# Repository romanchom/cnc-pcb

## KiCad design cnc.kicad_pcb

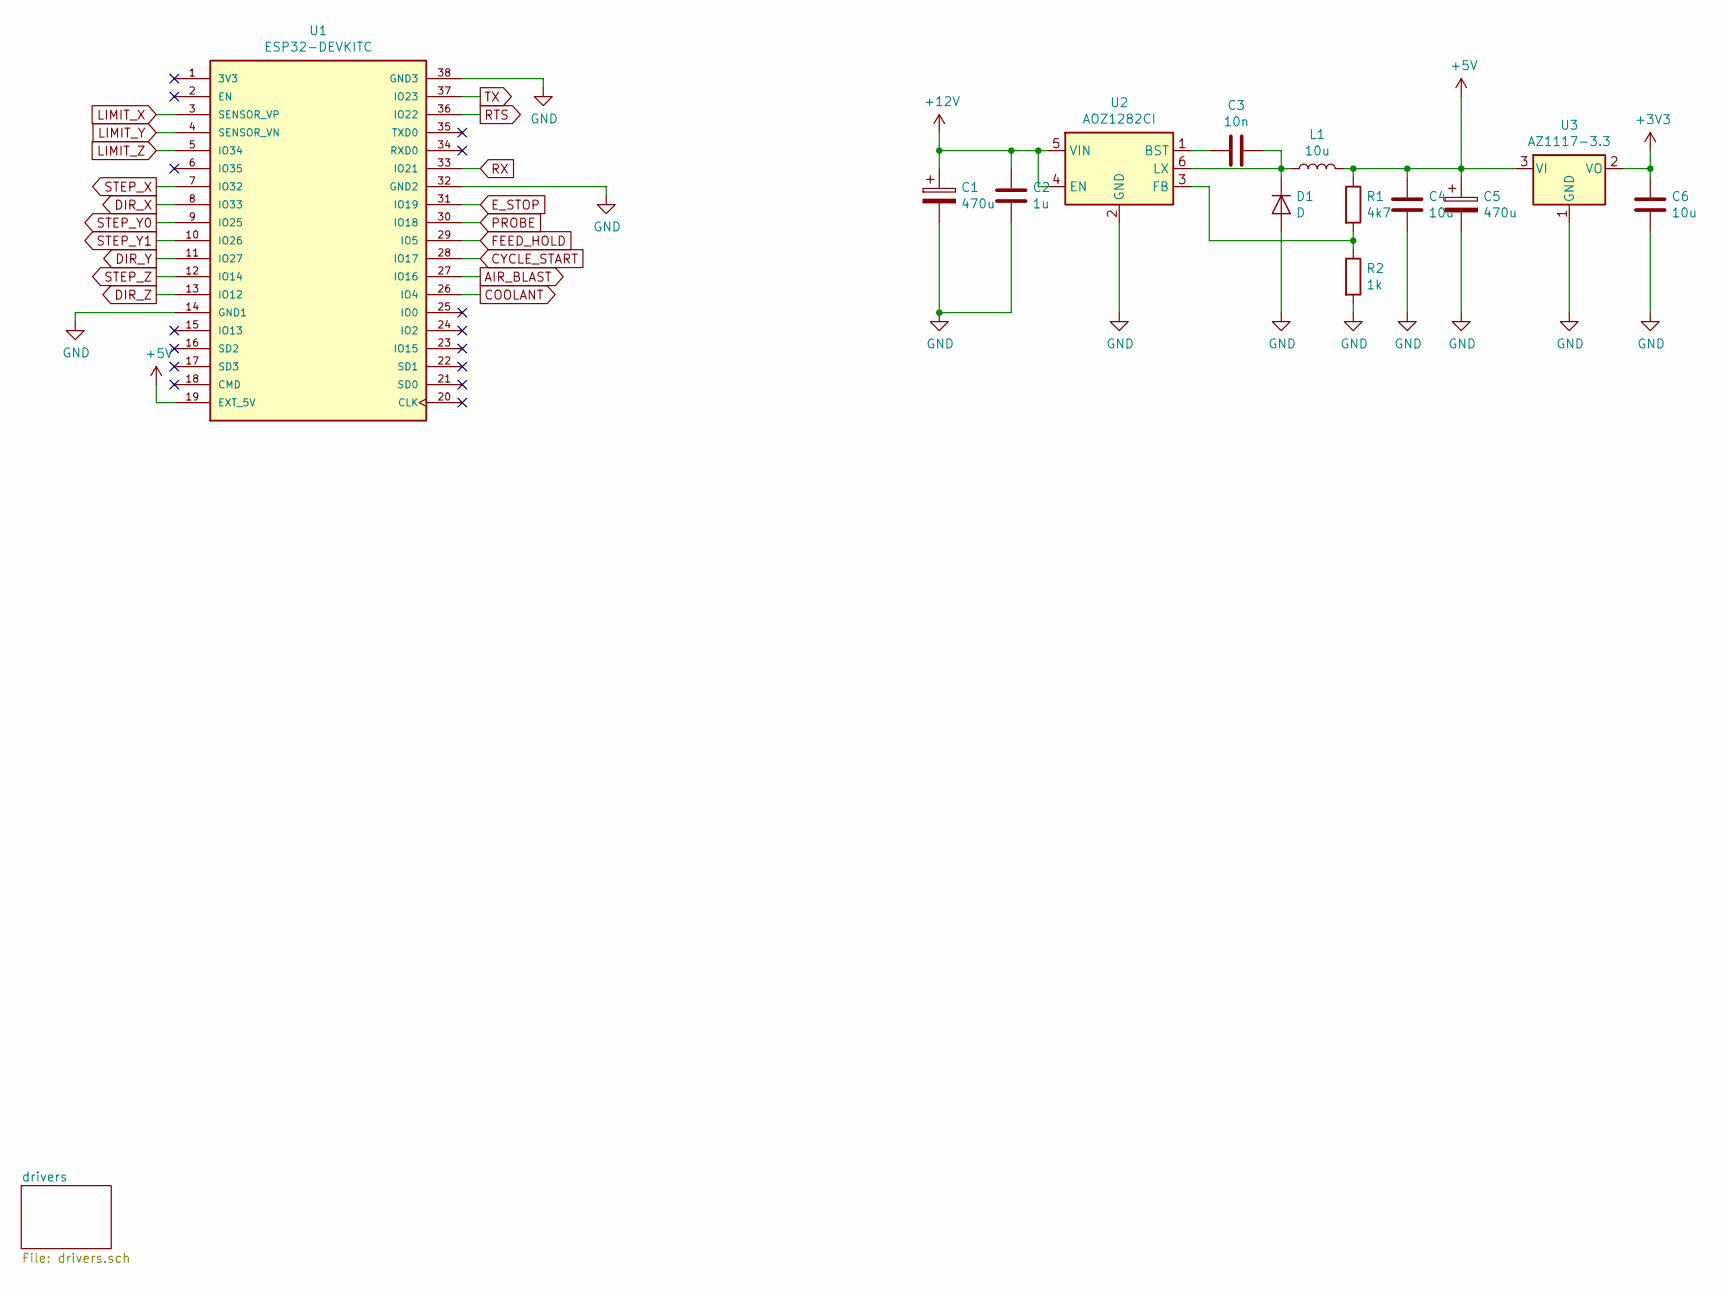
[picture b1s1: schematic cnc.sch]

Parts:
C1, C5: 470u; CP_Elec_8x10
C2: 1u; C_1206_3216Metric_Pad1.42x1.75mm_HandSolder
C3: 10n; C_1206_3216Metric_Pad1.42x1.75mm_HandSolder
C4, C6: 10u; C_1206_3216Metric_Pad1.42x1.75mm_HandSolder
D1: D; D_SMA_Handsoldering
L1: 10u; L_Bourns-SRN4018
R1: 4k7; R_1206_3216Metric_Pad1.42x1.75mm_HandSolder
R2: 1k; R_1206_3216Metric_Pad1.42x1.75mm_HandSolder
U1: ESP32-DEVKITC; MODULE_ESP32-DEVKITC; PARTREV N/A
U2: AOZ1282CI; SOT-23-6
U3: AZ1117-3.3; SOT-223-3_TabPin2

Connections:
+3V3: C6.1, U3.2 (VO); also elsewhere on the board
+5V: C4.1, C5.1, L1.2, R1.1, U1.19 (EXT_5V), U3.3 (VI)
+12V: C1.1, C2.1, U2.4 (EN), U2.5 (VIN); also elsewhere on the board
AIR_BLAST: U1.27 (IO16); also elsewhere on the board
COOLANT: U1.26 (IO4); also elsewhere on the board
CYCLE_START: U1.28 (IO17); also elsewhere on the board
DIR_X: U1.8 (IO33); also elsewhere on the board
DIR_Y: U1.11 (IO27); also elsewhere on the board
DIR_Z: U1.13 (IO12); also elsewhere on the board
E_STOP: U1.31 (IO19); also elsewhere on the board
FEED_HOLD: U1.29 (IO5); also elsewhere on the board
GND: C1.2, C2.2, C4.2, C5.2, C6.2, D1.2 (A), R2.2, U1.14 (GND1), U1.32 (GND2), U1.38 (GND3), U2.2 (GND), U3.1 (GND); also elsewhere on the board
LIMIT_X: U1.3 (SENSOR_VP); also elsewhere on the board
LIMIT_Y: U1.4 (SENSOR_VN); also elsewhere on the board
LIMIT_Z: U1.5 (IO34); also elsewhere on the board
unnamed: C3.1, U2.1 (BST)
unnamed: C3.2, D1.1 (K), L1.1, U2.6 (LX)
unnamed: R1.2, R2.1, U2.3 (FB)
PROBE: U1.30 (IO18); also elsewhere on the board
RTS: U1.36 (IO22); also elsewhere on the board
RX: U1.33 (IO21); also elsewhere on the board
STEP_X: U1.7 (IO32); also elsewhere on the board
STEP_Y0: U1.9 (IO25); also elsewhere on the board
STEP_Y1: U1.10 (IO26); also elsewhere on the board
STEP_Z: U1.12 (IO14); also elsewhere on the board
TX: U1.37 (IO23); also elsewhere on the board

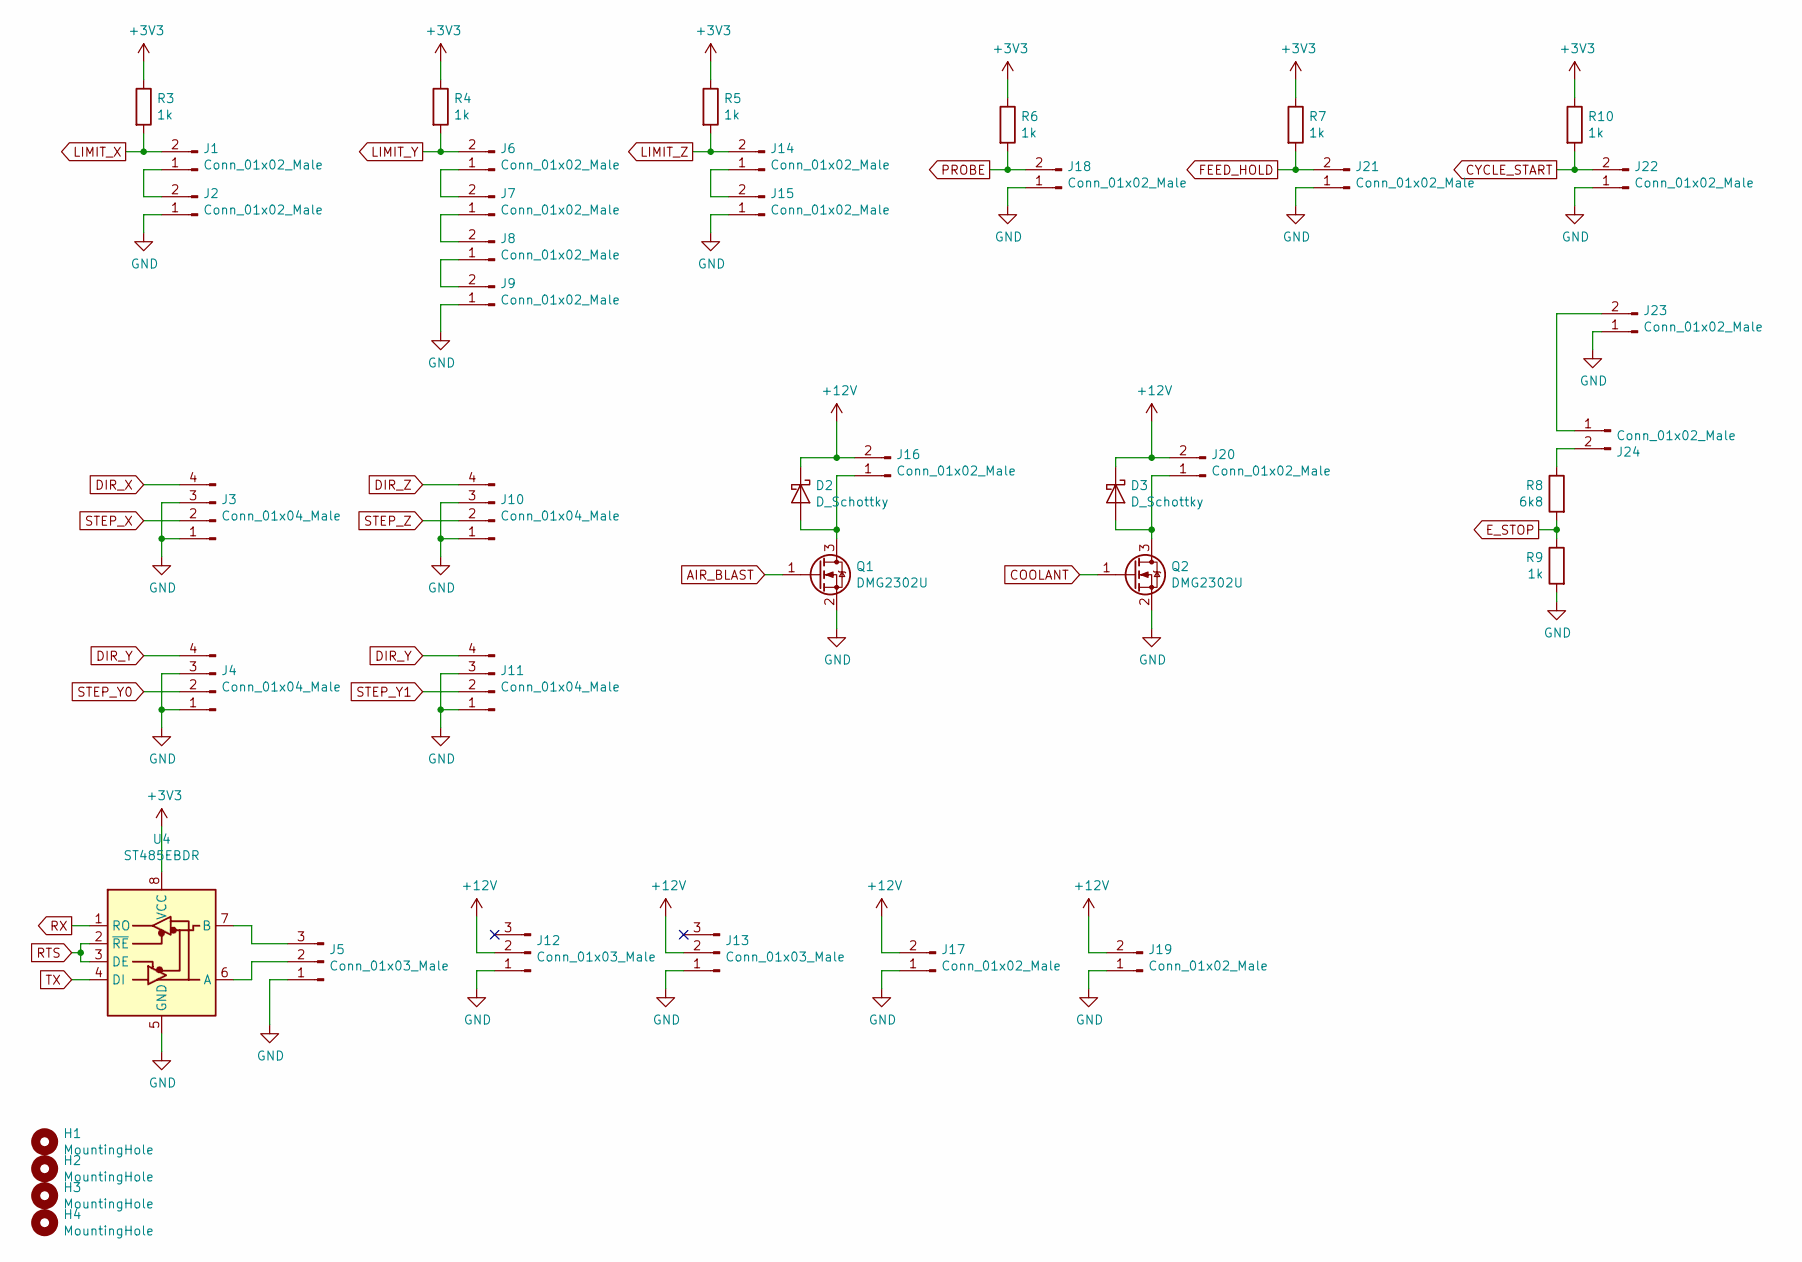
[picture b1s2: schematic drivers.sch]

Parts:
D2, D3: D_Schottky; D_SMA_Handsoldering
H1, H2, H3, H4: MountingHole; MountingHole_3.2mm_M3
J1, J2, J6, J7, J8, J9, J14, J15, J16, J17, J18, J19, J20, J21, J22, J23, J24: Conn_01x02_Male; Molex_KK-254_AE-6410-02A_1x02_P2.54mm_Vertical
J3, J4, J10, J11: Conn_01x04_Male; Molex_KK-254_AE-6410-04A_1x04_P2.54mm_Vertical
J5, J12, J13: Conn_01x03_Male; Molex_KK-254_AE-6410-03A_1x03_P2.54mm_Vertical
Q1, Q2: DMG2302U; SOT-23
R3, R4, R5, R6, R7, R9, R10: 1k; R_1206_3216Metric_Pad1.42x1.75mm_HandSolder
R8: 6k8; R_1206_3216Metric_Pad1.42x1.75mm_HandSolder
U4: ST485EBDR; SOIC-8_3.9x4.9mm_P1.27mm

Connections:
+3V3: R3.1, R4.1, R5.1, R6.1, R7.1, R10.1, U4.8 (VCC); also elsewhere on the board
+12V: D2.1 (K), D3.1 (K), J12.2, J13.2, J16.2, J17.2, J19.2, J20.2; also elsewhere on the board
AIR_BLAST: Q1.1 (G); also elsewhere on the board
COOLANT: Q2.1 (G); also elsewhere on the board
CYCLE_START: J22.2, R10.2; also elsewhere on the board
DIR_X: J3.4; also elsewhere on the board
DIR_Y: J4.4, J11.4; also elsewhere on the board
DIR_Z: J10.4; also elsewhere on the board
E_STOP: R8.2, R9.1; also elsewhere on the board
FEED_HOLD: J21.2, R7.2; also elsewhere on the board
GND: J2.1, J3.1, J3.3, J4.1, J4.3, J5.1, J9.1, J10.1, J10.3, J11.1, J11.3, J12.1, J13.1, J15.1, J17.1, J18.1, J19.1, J21.1, J22.1, J23.1, Q1.2 (S), Q2.2 (S), R9.2, U4.5 (GND); also elsewhere on the board
LIMIT_X: J1.2, R3.2; also elsewhere on the board
LIMIT_Y: J6.2, R4.2; also elsewhere on the board
LIMIT_Z: J14.2, R5.2; also elsewhere on the board
unnamed: D2.2 (A), J16.1, Q1.3 (D)
unnamed: D3.2 (A), J20.1, Q2.3 (D)
unnamed: J1.1, J2.2
unnamed: J5.2, U4.6 (A)
unnamed: J5.3, U4.7 (B)
unnamed: J6.1, J7.2
unnamed: J7.1, J8.2
unnamed: J8.1, J9.2
unnamed: J14.1, J15.2
unnamed: J23.2, J24.1
unnamed: J24.2, R8.1
PROBE: J18.2, R6.2; also elsewhere on the board
RTS: U4.2 (~RE), U4.3 (DE); also elsewhere on the board
RX: U4.1 (RO); also elsewhere on the board
STEP_X: J3.2; also elsewhere on the board
STEP_Y0: J4.2; also elsewhere on the board
STEP_Y1: J11.2; also elsewhere on the board
STEP_Z: J10.2; also elsewhere on the board
TX: U4.4 (DI); also elsewhere on the board

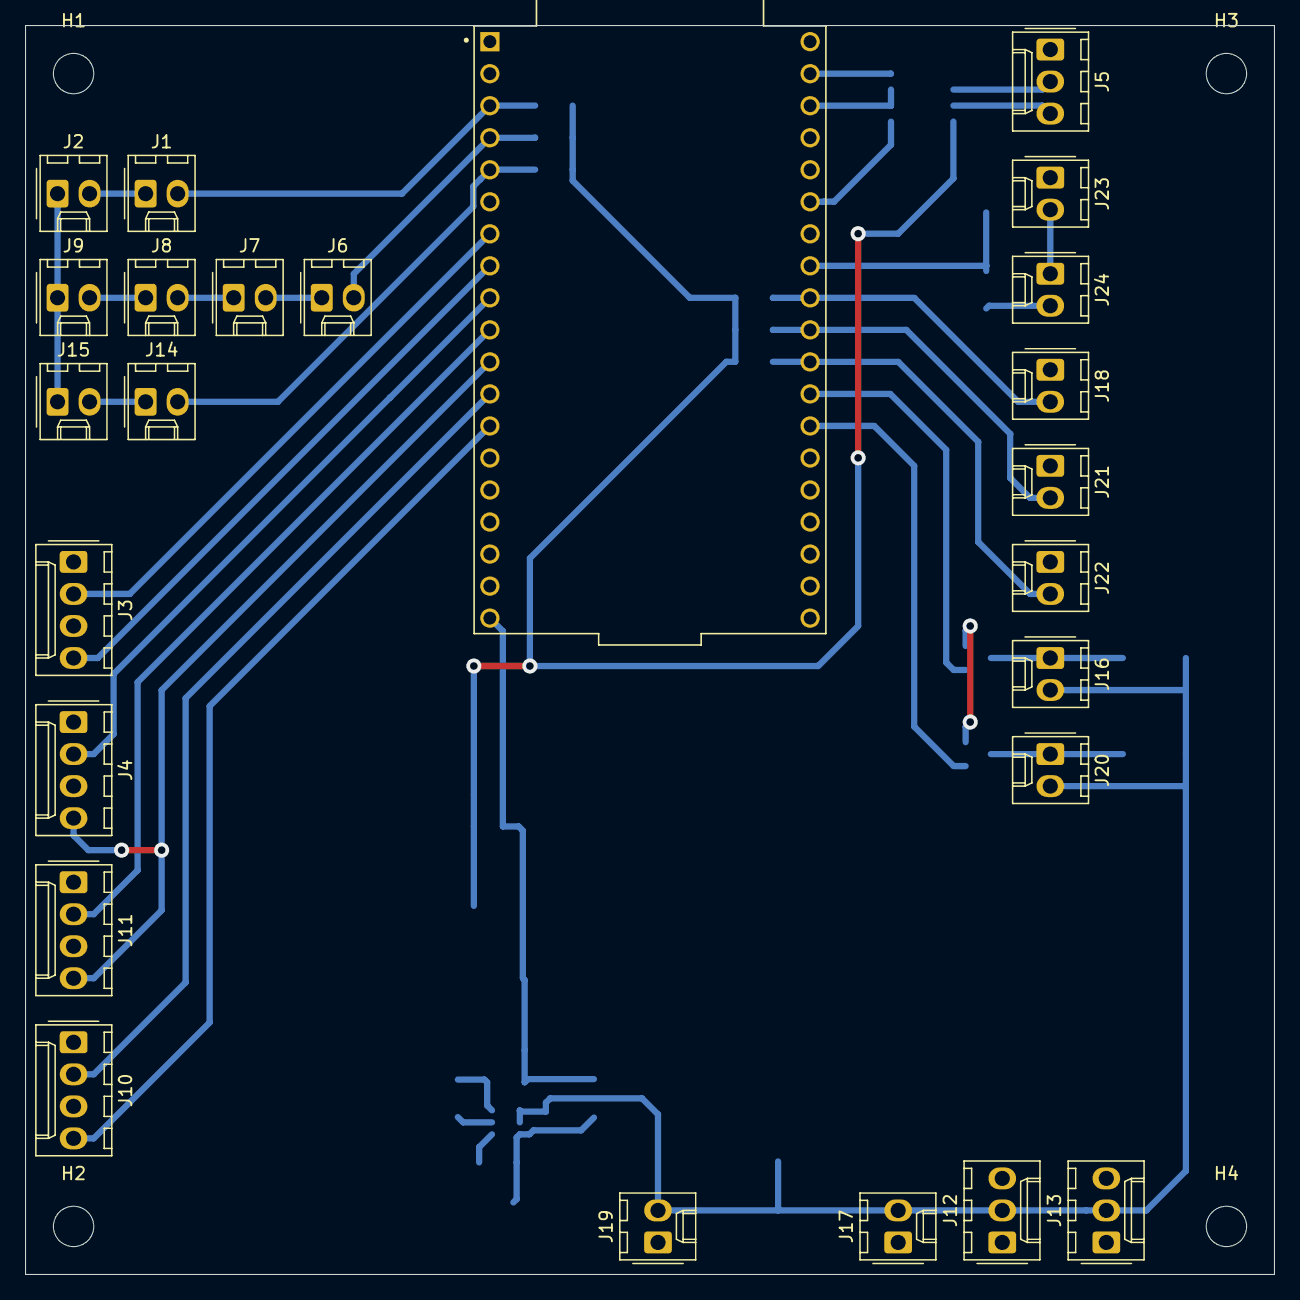
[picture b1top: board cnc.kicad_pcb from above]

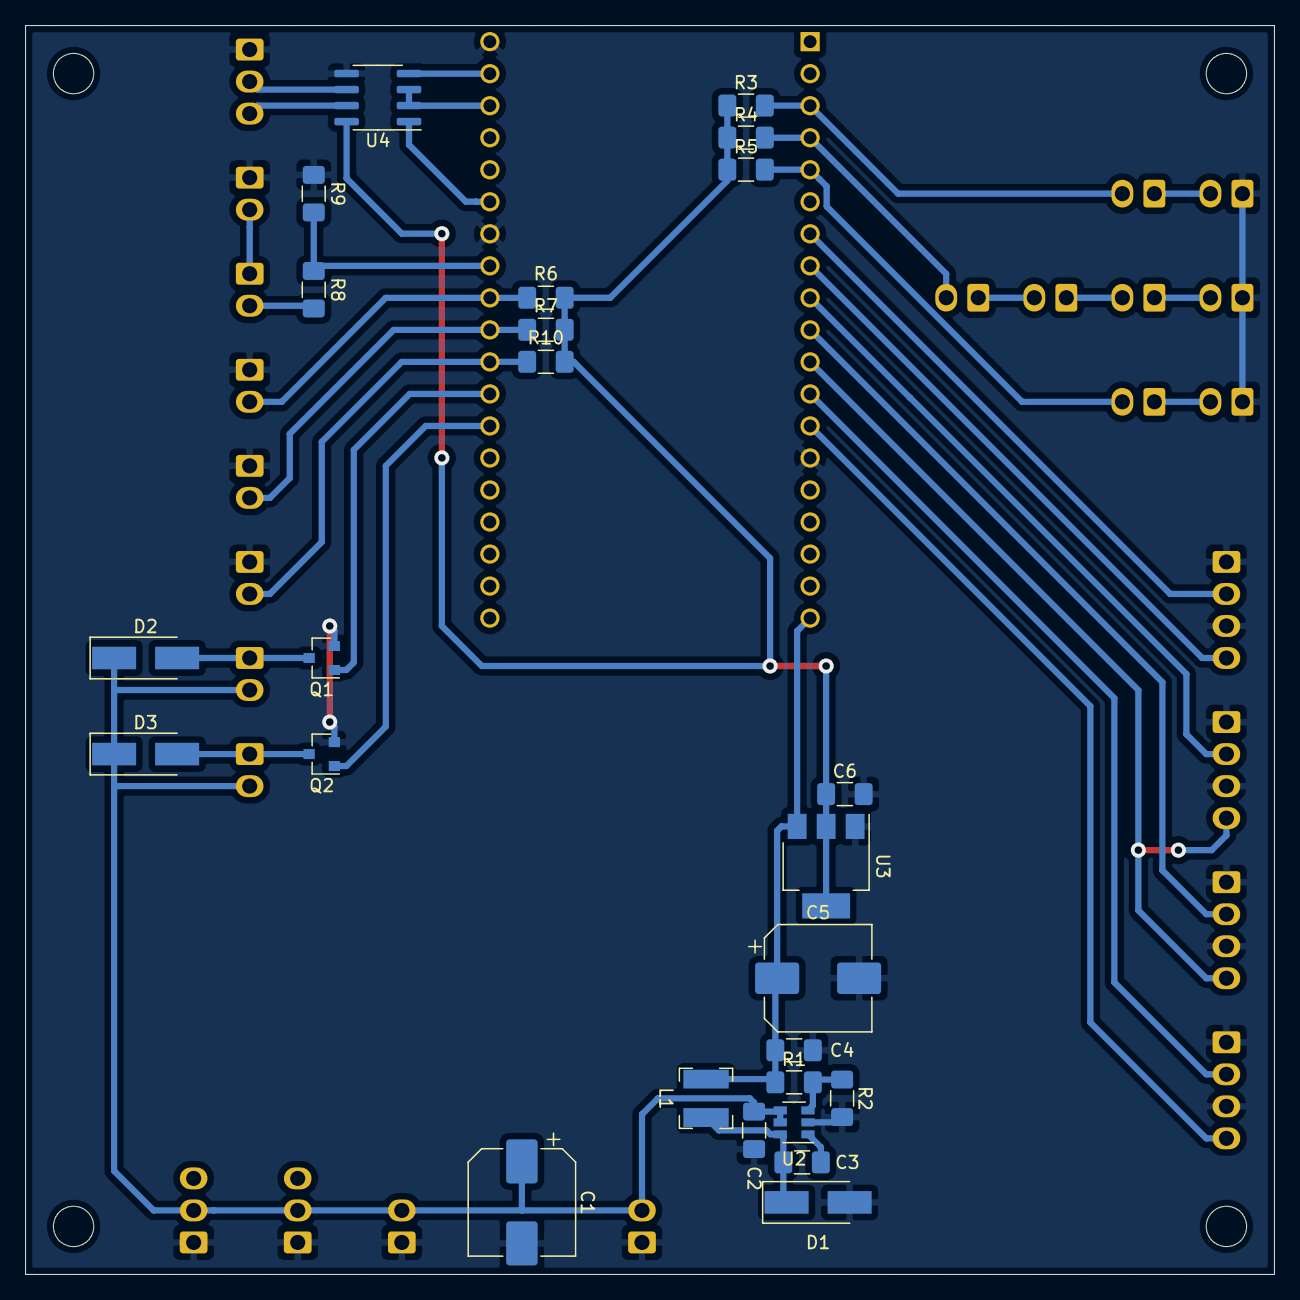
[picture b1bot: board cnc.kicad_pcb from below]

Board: 2 copper layers, 99.1 x 99.1 mm, 54 parts (25 on the bottom side), 37 nets.

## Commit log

2020-11-23 Initial version
2021-08-16 External drivers
2021-08-18 Fixes
